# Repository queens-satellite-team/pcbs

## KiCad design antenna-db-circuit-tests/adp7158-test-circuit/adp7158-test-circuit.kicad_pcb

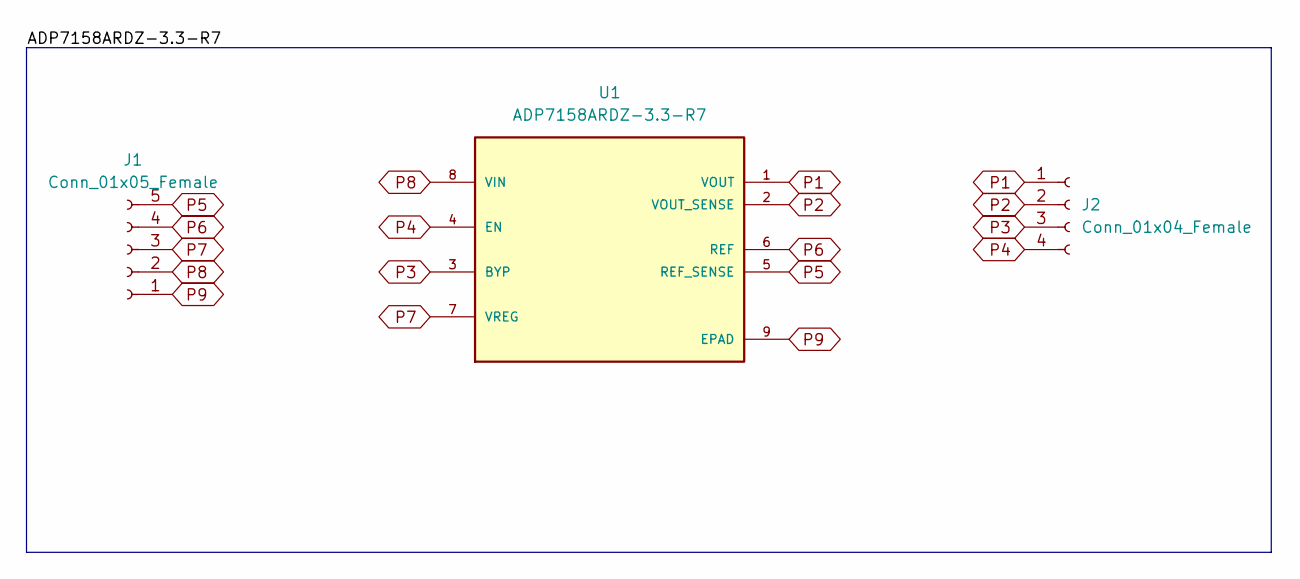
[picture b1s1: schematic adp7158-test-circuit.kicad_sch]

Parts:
J1: Conn_01x05_Female; PinHeader_1x05_P2.54mm_Vertical
J2: Conn_01x04_Female; PinHeader_1x04_P2.54mm_Vertical
U1: ADP7158ARDZ-3.3-R7; SOIC127P600X175-9N; PARTREV C

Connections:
P1: J2.1, U1.1 (VOUT)
P2: J2.2, U1.2 (VOUT_SENSE)
P3: J2.3, U1.3 (BYP)
P4: J2.4, U1.4 (EN)
P5: J1.5, U1.5 (REF_SENSE)
P6: J1.4, U1.6 (REF)
P7: J1.3, U1.7 (VREG)
P8: J1.2, U1.8 (VIN)
P9: J1.1, U1.9 (EPAD)

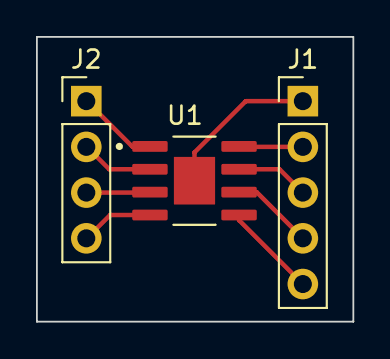
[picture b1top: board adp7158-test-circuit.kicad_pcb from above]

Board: 2 copper layers, 17.6 x 15.8 mm, 3 parts (0 on the bottom side), 9 nets.

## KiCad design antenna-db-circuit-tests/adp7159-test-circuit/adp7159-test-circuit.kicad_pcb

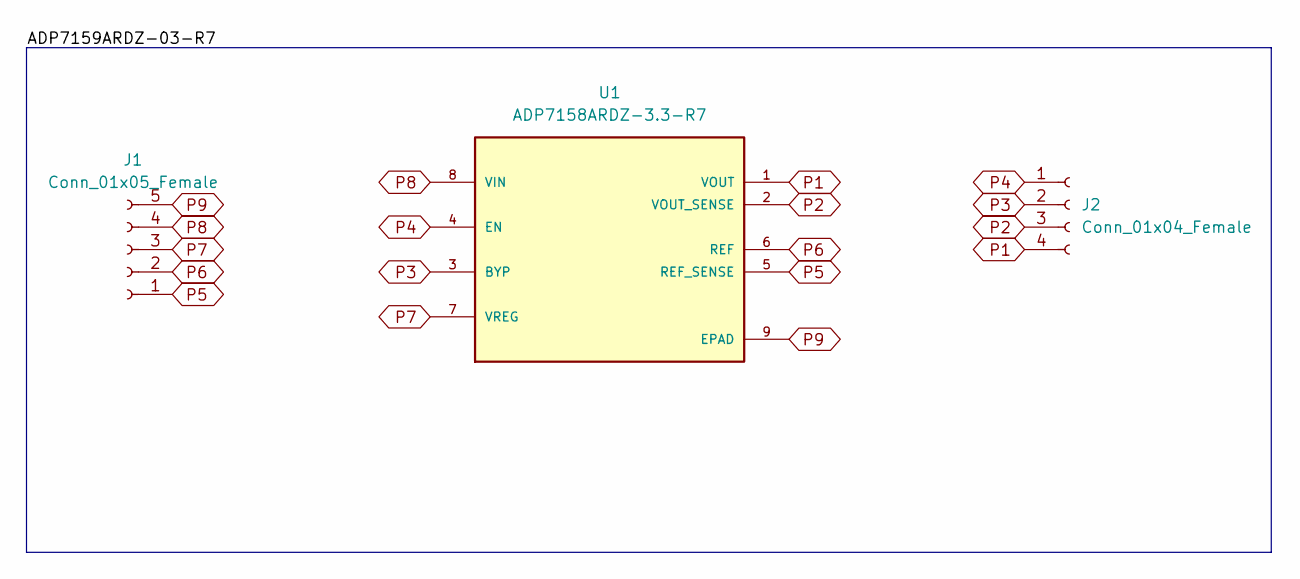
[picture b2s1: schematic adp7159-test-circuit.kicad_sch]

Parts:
J1: Conn_01x05_Female; PinHeader_1x05_P2.54mm_Vertical
J2: Conn_01x04_Female; PinHeader_1x04_P2.54mm_Vertical
U1: ADP7158ARDZ-3.3-R7; SOIC127P600X175-9N; PARTREV C

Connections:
P1: J2.4, U1.1 (VOUT)
P2: J2.3, U1.2 (VOUT_SENSE)
P3: J2.2, U1.3 (BYP)
P4: J2.1, U1.4 (EN)
P5: J1.1, U1.5 (REF_SENSE)
P6: J1.2, U1.6 (REF)
P7: J1.3, U1.7 (VREG)
P8: J1.4, U1.8 (VIN)
P9: J1.5, U1.9 (EPAD)

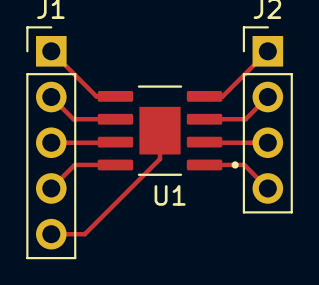
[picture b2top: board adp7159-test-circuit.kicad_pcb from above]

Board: 2 copper layers, 3 parts (0 on the bottom side), 9 nets.

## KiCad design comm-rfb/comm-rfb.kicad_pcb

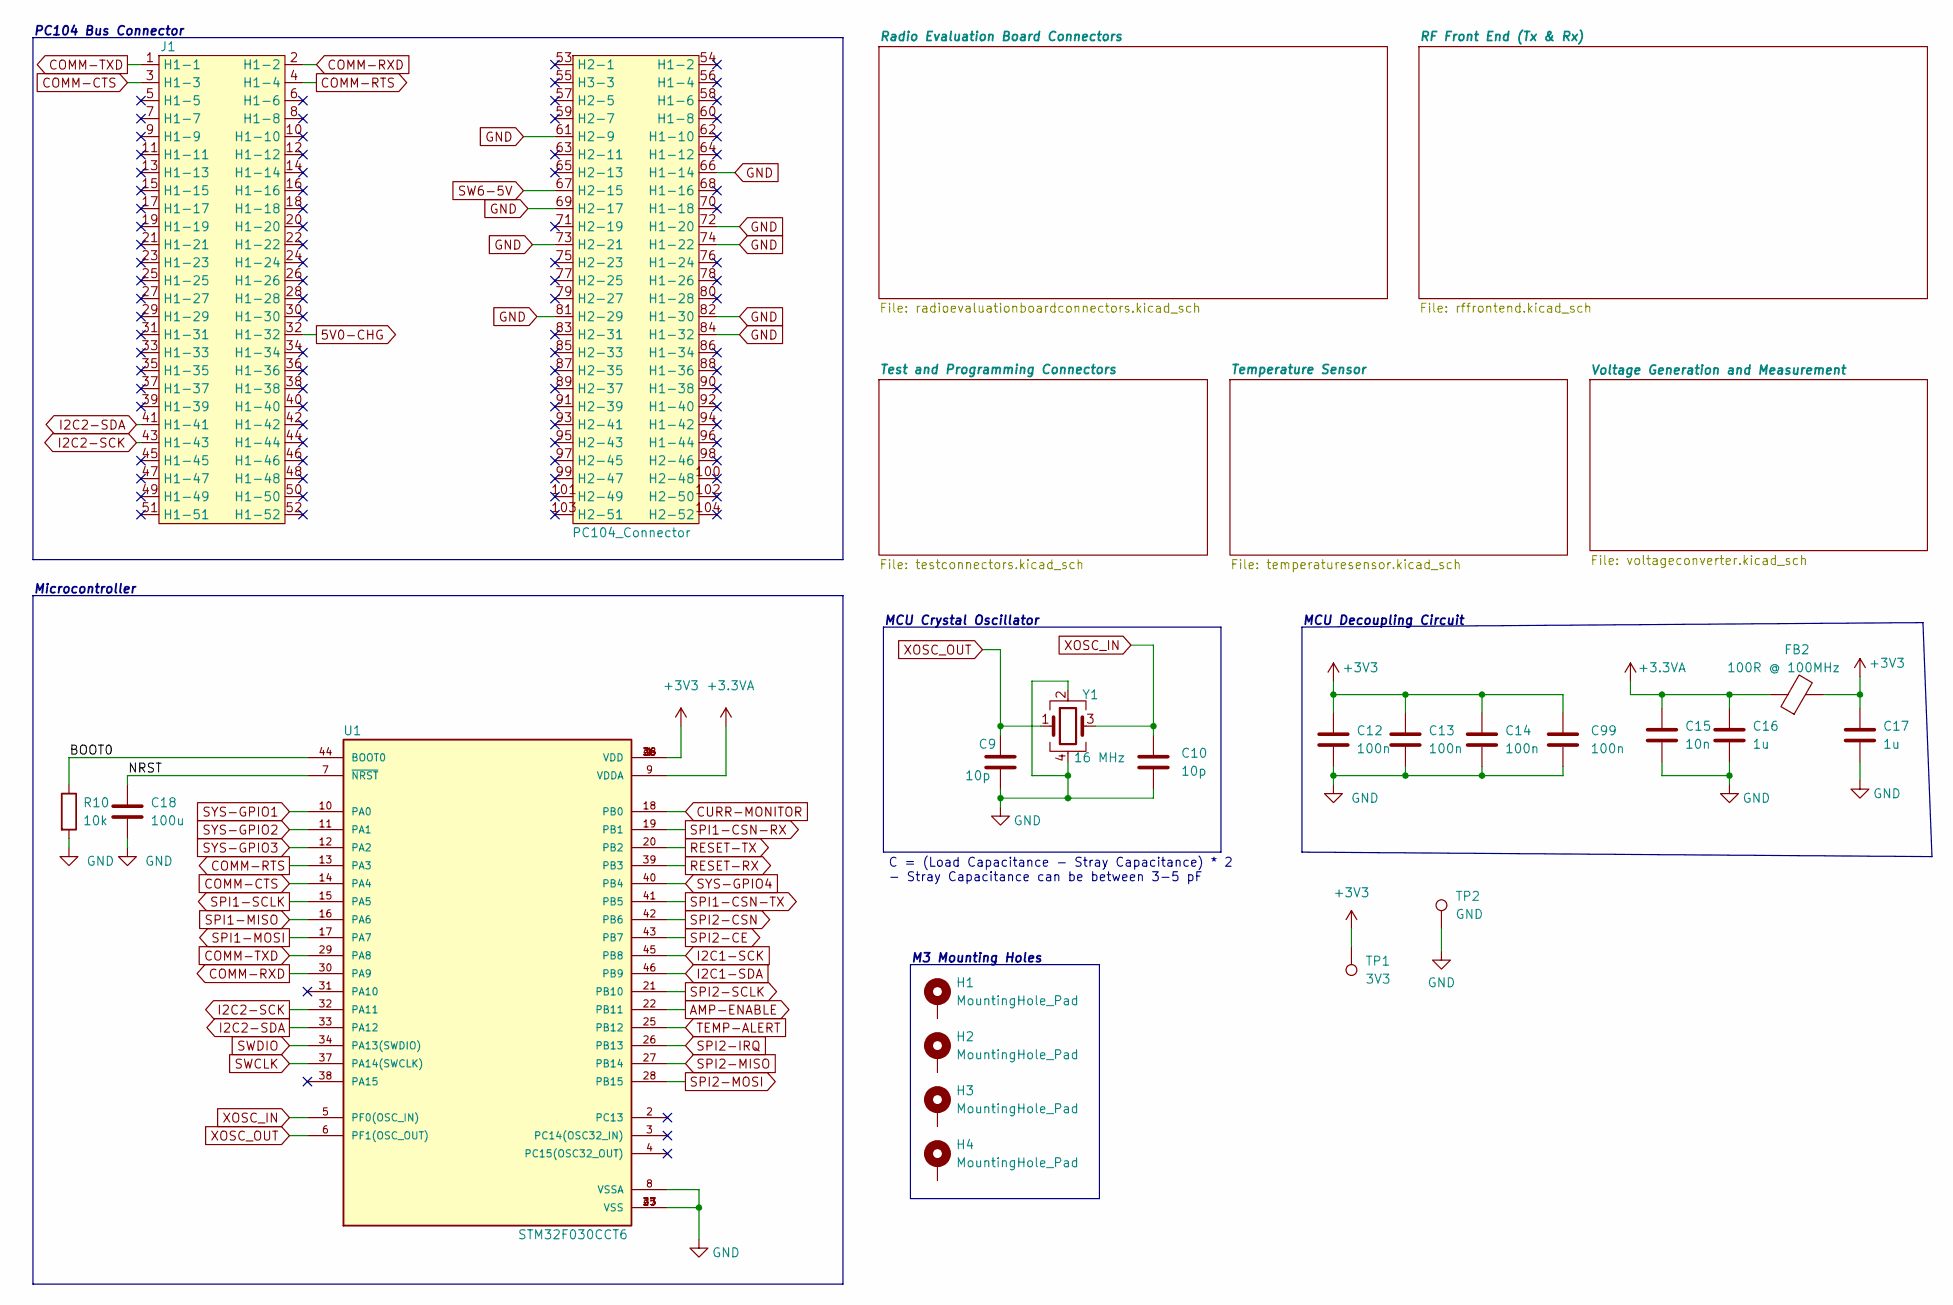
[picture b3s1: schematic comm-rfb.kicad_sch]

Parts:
C9, C10: 10p; C_0603_1608Metric
C12, C13, C14, C99: 100n; C_0603_1608Metric
C15: 10n; C_0603_1608Metric
C16, C17: 1u; C_0603_1608Metric
C18: 100u; C_0603_1608Metric
FB2: 100R @ 100MHz; L_0603_1608Metric
H1, H2, H3, H4: MountingHole_Pad; MountingHole_3.2mm_M3_Pad_TopBottom
J1: PC104_Connector; pc104-connector
R10: 10k; R_0603_1608Metric
TP1: 3V3; TestPoint_Pad_D2.0mm
TP2: GND; TestPoint_Pad_D2.0mm
U1: STM32F030CCT6; QFP50P900X900X160-48N
Y1: 16 MHz; Crystal_SMD_3225-4Pin_3.2x2.5mm

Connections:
5V0-CHG: J1.32 (H1-32); also elsewhere on the board
+3.3VA: C15.1, C16.1, FB2.1, U1.9 (VDDA)
+3V3: C12.1, C13.1, C14.1, C17.1, C99.1, FB2.2, TP1.1, U1.1 (VDD), U1.24 (VDD), U1.36 (VDD), U1.48 (VDD); also elsewhere on the board
/BOOT0: R10.1, U1.44 (BOOT0)
/NRST: C18.1, U1.7 (~NRST)
AMP-ENABLE: U1.22 (PB11); also elsewhere on the board
COMM-CTS: J1.3 (H1-3), U1.14 (PA4)
COMM-RTS: J1.4 (H1-4), U1.13 (PA3)
COMM-RXD: J1.2 (H1-2), U1.30 (PA9)
COMM-TXD: J1.1 (H1-1), U1.29 (PA8)
CURR-MONITOR: U1.18 (PB0); also elsewhere on the board
I2C1-SCK: U1.45 (PB8)
I2C1-SDA: U1.46 (PB9)
I2C2-SCK: J1.43 (H1-43), U1.32 (PA11); also elsewhere on the board
I2C2-SDA: J1.41 (H1-41), U1.33 (PA12); also elsewhere on the board
RESET-RX: U1.39 (PB3); also elsewhere on the board
RESET-TX: U1.20 (PB2); also elsewhere on the board
SPI1-CSN-RX: U1.19 (PB1); also elsewhere on the board
SPI1-CSN-TX: U1.41 (PB5); also elsewhere on the board
SPI1-MISO: U1.16 (PA6); also elsewhere on the board
SPI1-MOSI: U1.17 (PA7); also elsewhere on the board
SPI1-SCLK: U1.15 (PA5); also elsewhere on the board
SPI2-CE: U1.43 (PB7); also elsewhere on the board
SPI2-CSN: U1.42 (PB6); also elsewhere on the board
SPI2-IRQ: U1.26 (PB13); also elsewhere on the board
SPI2-MISO: U1.27 (PB14); also elsewhere on the board
SPI2-MOSI: U1.28 (PB15); also elsewhere on the board
SPI2-SCLK: U1.21 (PB10); also elsewhere on the board
SW6-5V: J1.67 (H2-15); also elsewhere on the board
SWCLK: U1.37 (PA14(SWCLK)); also elsewhere on the board
SWDIO: U1.34 (PA13(SWDIO)); also elsewhere on the board
SYS-GPIO1: U1.10 (PA0); also elsewhere on the board
SYS-GPIO2: U1.11 (PA1); also elsewhere on the board
SYS-GPIO3: U1.12 (PA2); also elsewhere on the board
SYS-GPIO4: U1.40 (PB4); also elsewhere on the board
TEMP-ALERT: U1.25 (PB12); also elsewhere on the board
XOSC_IN: C10.1, U1.5 (PF0(OSC_IN)), Y1.3
XOSC_OUT: C9.1, U1.6 (PF1(OSC_OUT)), Y1.1

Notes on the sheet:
M3 Mounting Holes
MCU Crystal Oscillator
C = (Load Capacitance - Stray Capacitance) * 2 - Stray Capacitance can be between 3-5 pF
PC104 Bus Connector
MCU Decoupling Circuit
Microcontroller

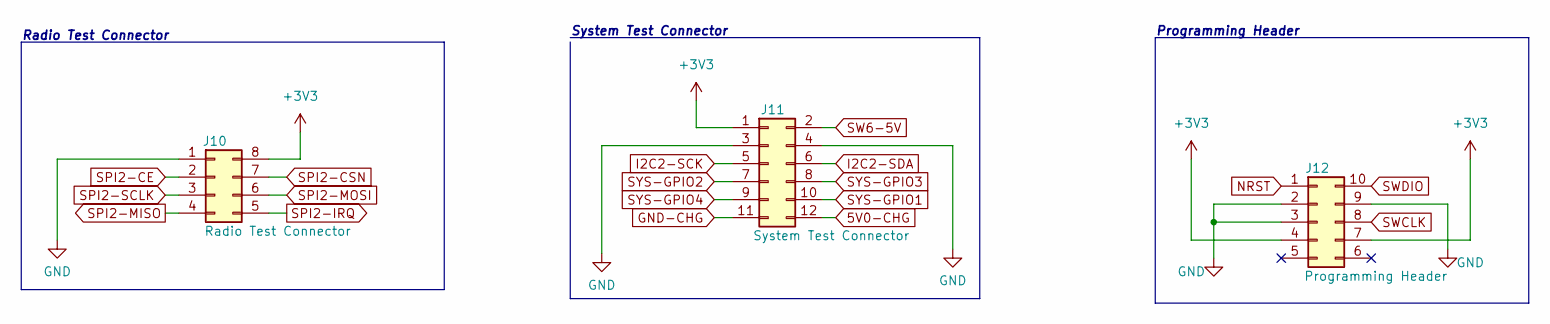
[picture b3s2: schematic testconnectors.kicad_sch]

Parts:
J10: Radio Test Connector; PinSocket_2x04_P2.54mm_Vertical
J11: System Test Connector; PinSocket_2x06_P2.54mm_Horizontal
J12: Programming Header; PinSocket_2x05_P2.54mm_Horizontal

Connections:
5V0-CHG: J11.12; also elsewhere on the board
+3V3: J10.8, J11.1, J12.4, J12.7; also elsewhere on the board
I2C2-SCK: J11.5; also elsewhere on the board
I2C2-SDA: J11.6; also elsewhere on the board
NRST: J12.1
SPI2-CE: J10.2; also elsewhere on the board
SPI2-CSN: J10.7; also elsewhere on the board
SPI2-IRQ: J10.5; also elsewhere on the board
SPI2-MISO: J10.4; also elsewhere on the board
SPI2-MOSI: J10.6; also elsewhere on the board
SPI2-SCLK: J10.3; also elsewhere on the board
SW6-5V: J11.2; also elsewhere on the board
SWCLK: J12.8; also elsewhere on the board
SWDIO: J12.10; also elsewhere on the board
SYS-GPIO1: J11.10; also elsewhere on the board
SYS-GPIO2: J11.7; also elsewhere on the board
SYS-GPIO3: J11.8; also elsewhere on the board
SYS-GPIO4: J11.9; also elsewhere on the board

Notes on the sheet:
Radio Test Connector
Programming Header
System Test Connector

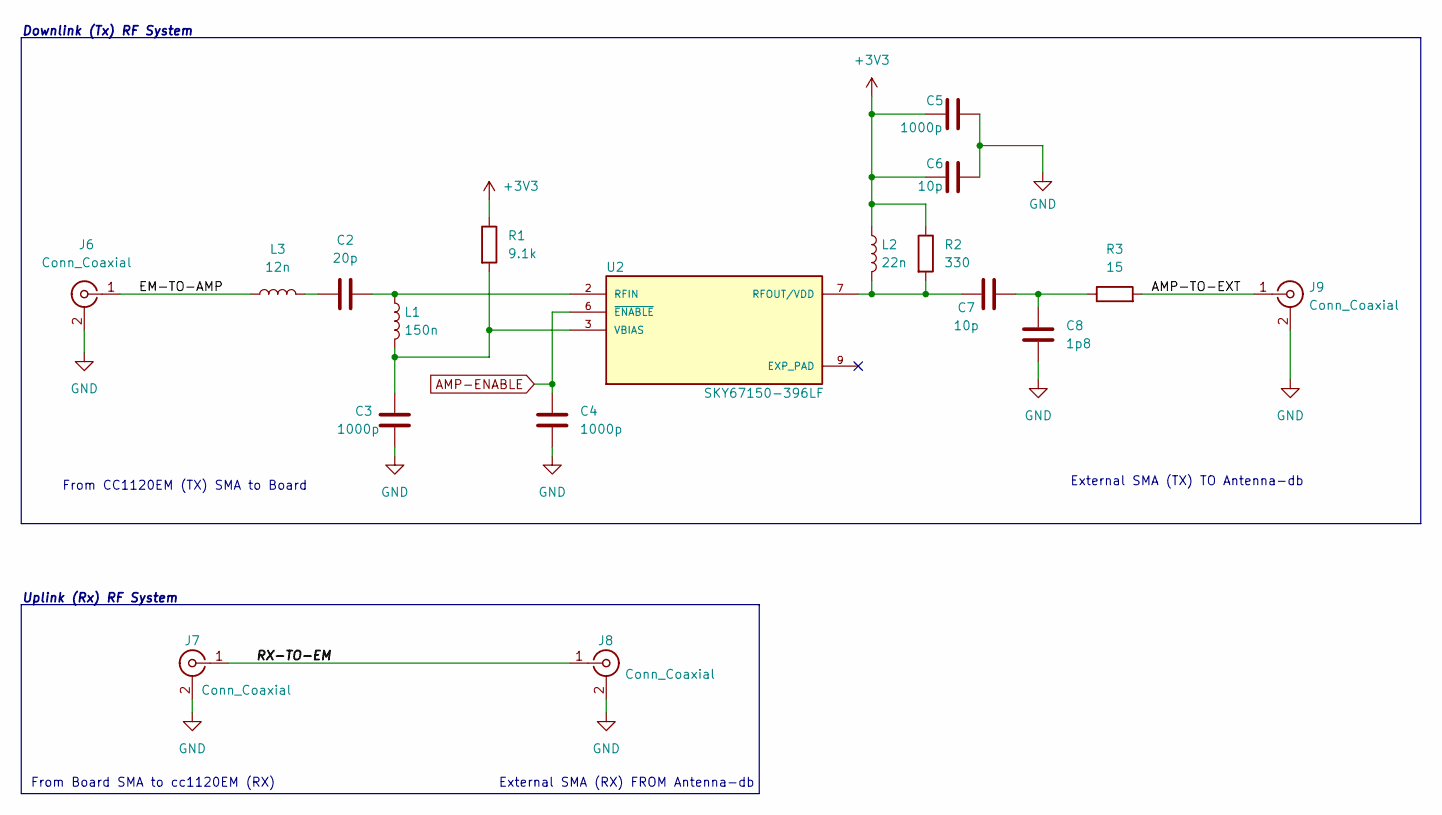
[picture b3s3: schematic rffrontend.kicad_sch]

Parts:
C2: 20p; C_0402_1005Metric
C3, C4, C5: 1000p; C_0402_1005Metric
C6, C7: 10p; C_0402_1005Metric
C8: 1p8; C_0402_1005Metric
J6, J7, J8, J9: Conn_Coaxial; SMA_Amphenol_132134-10_Vertical
L1: 150n; L_0402_1005Metric
L2: 22n; L_0402_1005Metric
L3: 12n; L_0402_1005Metric
R1: 9.1k; R_0603_1608Metric
R2: 330; R_0402_1005Metric
R3: 15; R_0402_1005Metric
U2: SKY67150-396LF; SON50P200X200X80-9N; PARTREV May 3,2017

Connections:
+3V3: C5.1, C6.1, L2.1, R1.1, R2.1; also elsewhere on the board
/RF Front End (Tx & Rx)/AMP-TO-EXT: J9.1 (In), R3.2
/RF Front End (Tx & Rx)/EM-TO-AMP: J6.1 (In), L3.1
/RF Front End (Tx & Rx)/RX-TO-EM: J7.1 (In), J8.1 (In)
AMP-ENABLE: C4.1, U2.6 (~ENABLE); also elsewhere on the board
unnamed: C2.1, L3.2
unnamed: C2.2, L1.1, U2.2 (RFIN)
unnamed: C3.1, L1.2, R1.2, U2.3 (VBIAS)
unnamed: C7.1, L2.2, R2.2, U2.7 (RFOUT/VDD)
unnamed: C7.2, C8.1, R3.1

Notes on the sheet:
Uplink (Rx) RF System
External SMA (TX) TO Antenna-db
Downlink (Tx) RF System
From CC1120EM (TX) SMA to Board
From Board SMA to cc1120EM (RX)
External SMA (RX) FROM Antenna-db

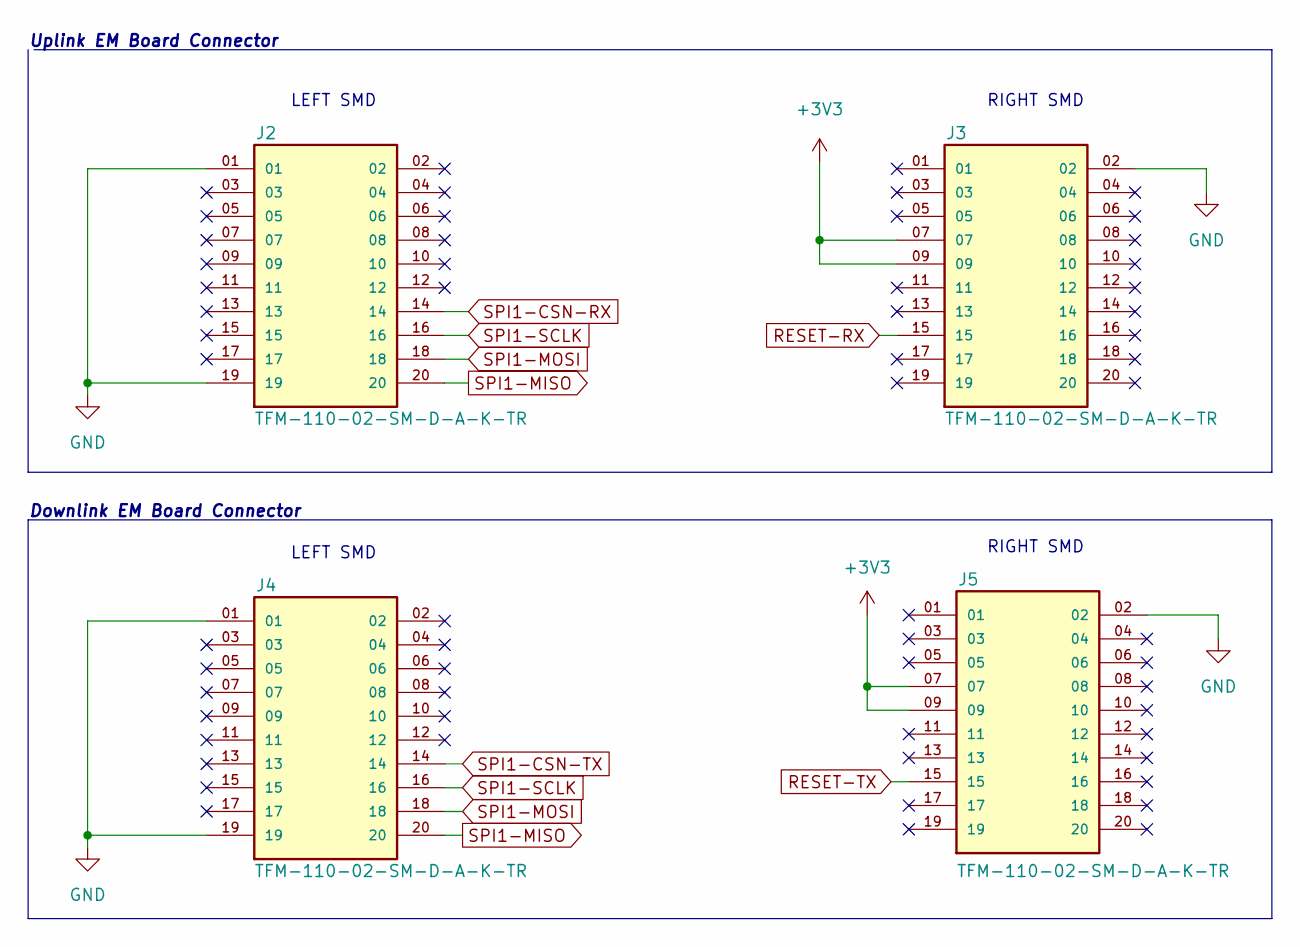
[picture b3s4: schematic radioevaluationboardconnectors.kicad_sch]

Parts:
J2, J3, J4, J5: TFM-110-02-SM-D-A-K-TR; SAMTEC_TFM-110-02-SM-D-A-K-TR; PARTREV R

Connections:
+3V3: J3.07, J3.09, J5.07, J5.09; also elsewhere on the board
RESET-RX: J3.15; also elsewhere on the board
RESET-TX: J5.15; also elsewhere on the board
SPI1-CSN-RX: J2.14; also elsewhere on the board
SPI1-CSN-TX: J4.14; also elsewhere on the board
SPI1-MISO: J2.20, J4.20; also elsewhere on the board
SPI1-MOSI: J2.18, J4.18; also elsewhere on the board
SPI1-SCLK: J2.16, J4.16; also elsewhere on the board

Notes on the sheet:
Downlink EM Board Connector
RIGHT SMD
LEFT SMD
Uplink EM Board Connector

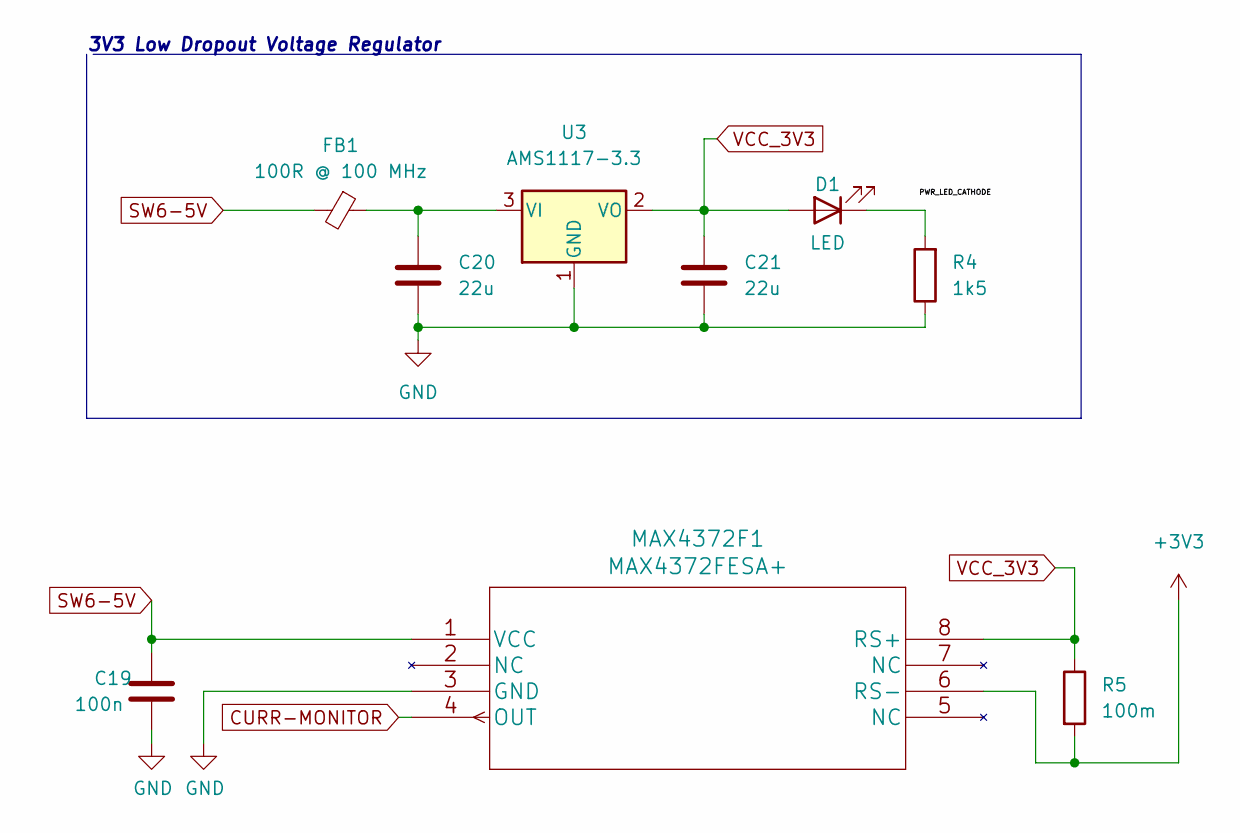
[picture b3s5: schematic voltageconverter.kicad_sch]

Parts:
C19: 100n; C_0603_1608Metric
C20, C21: 22u; C_0603_1608Metric
D1: LED; LED_0603_1608Metric
FB1: 100R @ 100 MHz; L_0603_1608Metric
MAX4372F1: MAX4372FESA+; SOIC127P600X175-8N
R4: 1k5; R_0603_1608Metric
R5: 100m; R_0603_1608Metric
U3: AMS1117-3.3; SOT-223-3_TabPin2

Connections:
+3V3: MAX4372F1.6 (RS-), R5.2; also elsewhere on the board
CURR-MONITOR: MAX4372F1.4 (OUT); also elsewhere on the board
unnamed: C20.1, FB1.1, U3.3 (VI)
unnamed: D1.1 (K), R4.2
SW6-5V: C19.1, FB1.2, MAX4372F1.1 (VCC); also elsewhere on the board
VCC_3V3: C21.1, D1.2 (A), MAX4372F1.8 (RS+), R5.1, U3.2 (VO)

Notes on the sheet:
3V3 Low Dropout Voltage Regulator

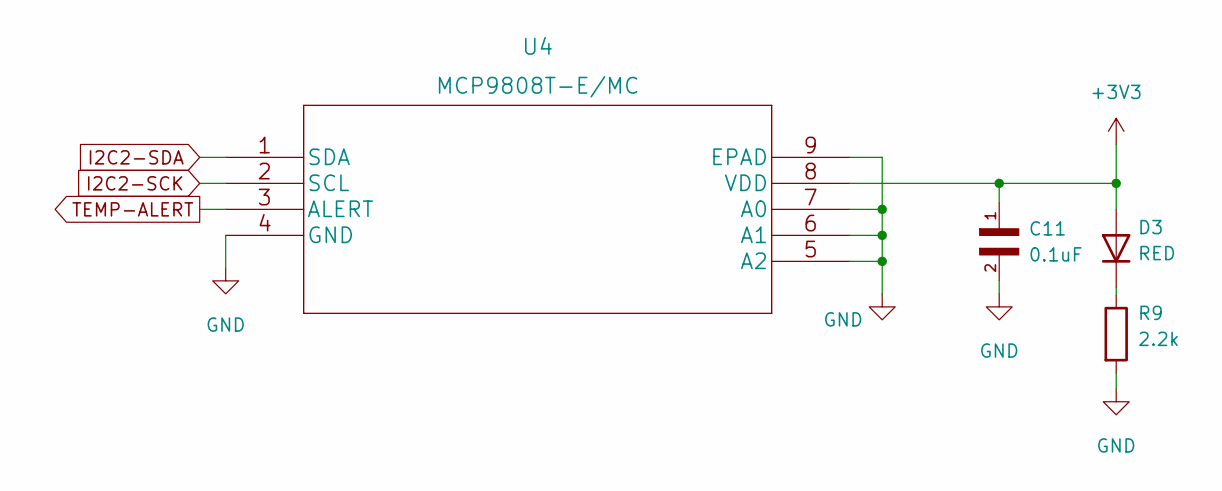
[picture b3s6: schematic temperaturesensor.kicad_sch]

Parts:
C11: 0.1uF; C_0603_1608Metric
D3: RED; D_0603_1608Metric
R9: 2.2k; R_0603_1608Metric
U4: MCP9808T-E/MC; MCP9808T-E&slash_MC

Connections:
+3V3: C11.1, D3.1 (A), U4.8 (VDD); also elsewhere on the board
I2C2-SCK: U4.2 (SCL); also elsewhere on the board
I2C2-SDA: U4.1 (SDA); also elsewhere on the board
unnamed: D3.2 (K), R9.1
TEMP-ALERT: U4.3 (ALERT); also elsewhere on the board

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
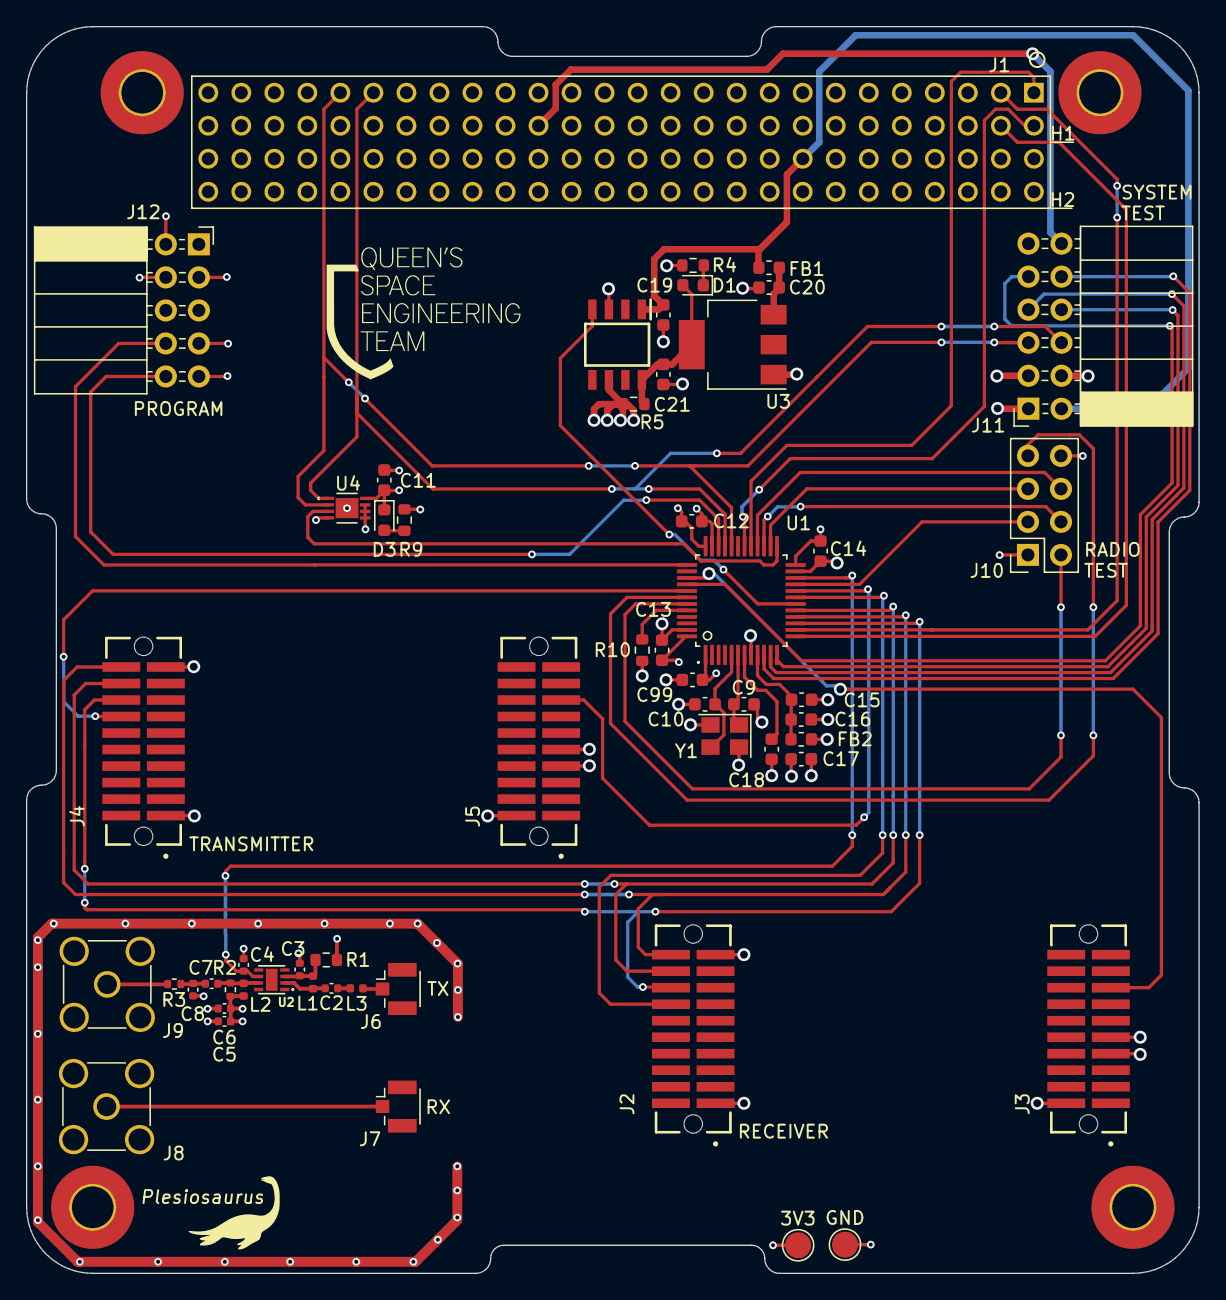
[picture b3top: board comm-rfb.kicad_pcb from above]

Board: 4 copper layers, 90.2 x 95.9 mm, 59 parts (0 on the bottom side), 49 nets.

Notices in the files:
parts and their libraries:
Copyright 2021 Accelerated Designs. All rights reserved.
